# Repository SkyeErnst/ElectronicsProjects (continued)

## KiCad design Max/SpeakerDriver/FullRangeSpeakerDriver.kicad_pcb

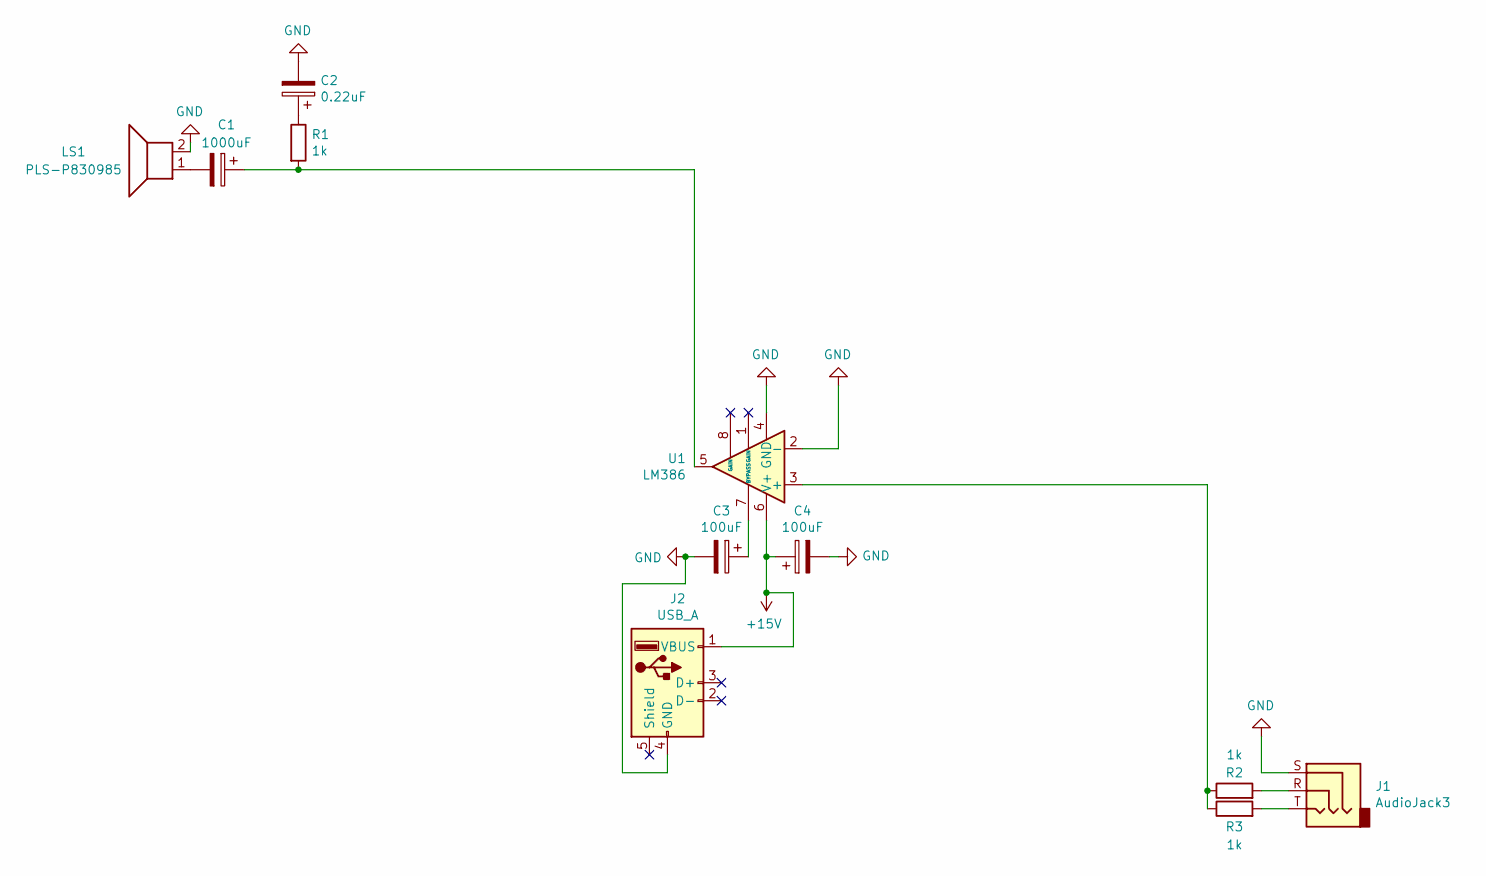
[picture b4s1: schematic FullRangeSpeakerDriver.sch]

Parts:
C1: 1000uF; CP_Radial_D10.0mm_P5.00mm
C2: 0.22uF; CP_Radial_D5.0mm_P2.50mm
C3, C4: 100uF; CP_Radial_D5.0mm_P2.50mm
J1: AudioJack3; PinSocket_1x03_P2.54mm_Vertical
J2: USB_A; USB_A_Stewart_SS-52100-001_Horizontal
LS1: PLS-P830985; PinSocket_1x02_P2.54mm_Vertical
R1, R2, R3: 1k; R_Axial_DIN0207_L6.3mm_D2.5mm_P10.16mm_Horizontal
U1: LM386; DIP-8_W7.62mm

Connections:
+15V: C4.1, J2.1 (VBUS), U1.6 (V+)
GND: C2.2, C3.2, C4.2, J1.S, J2.4 (GND), LS1.2, U1.2 (-), U1.4 (GND)
unnamed: C1.1, R1.2, U1.5
unnamed: C1.2, LS1.1
unnamed: C2.1, R1.1
unnamed: C3.1, U1.7 (BYPASS)
unnamed: J1.R, R2.2
unnamed: J1.T, R3.2
unnamed: R2.1, R3.1, U1.3 (+)

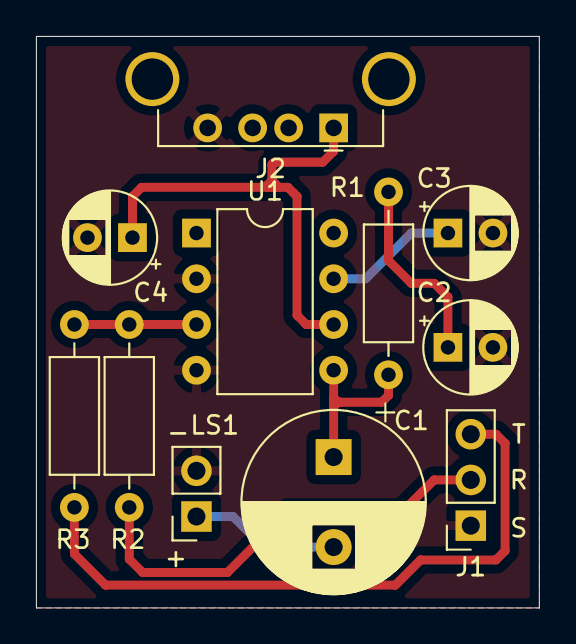
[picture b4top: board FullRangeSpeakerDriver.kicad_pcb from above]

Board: 2 copper layers, 27.9 x 31.7 mm, 11 parts (0 on the bottom side), 9 nets.

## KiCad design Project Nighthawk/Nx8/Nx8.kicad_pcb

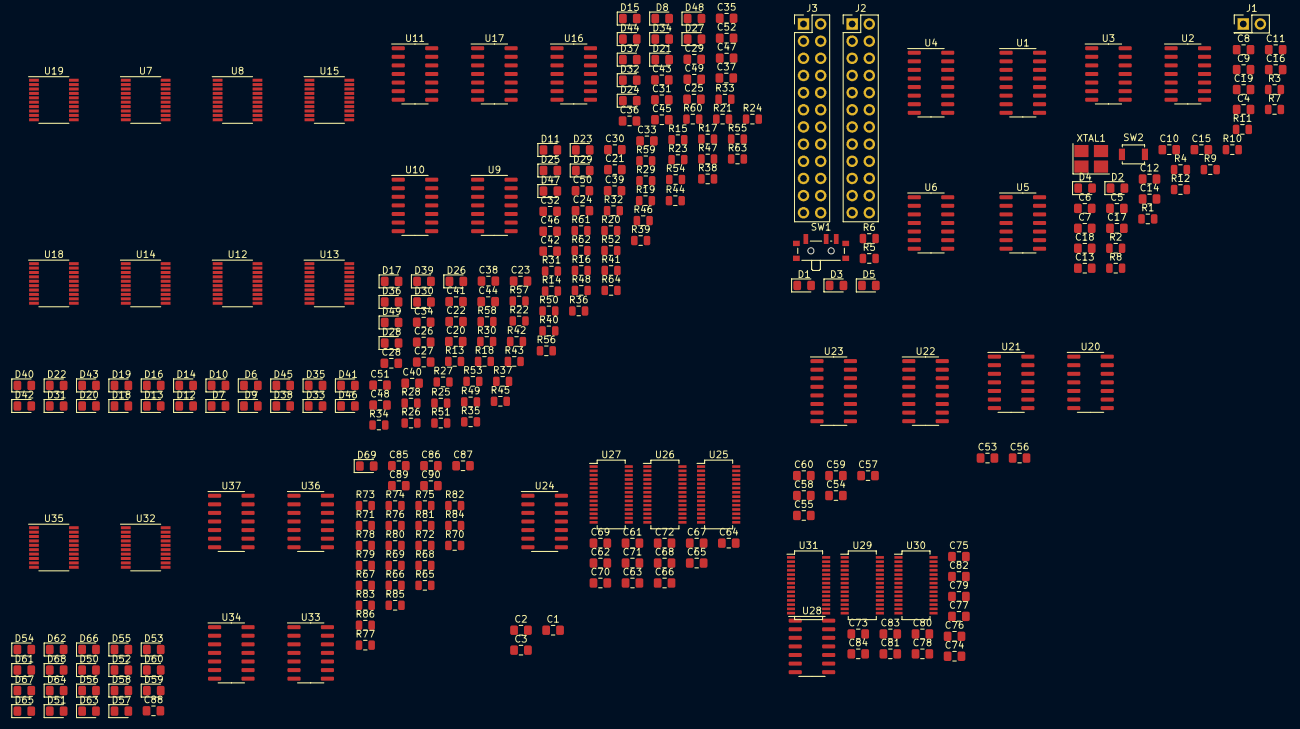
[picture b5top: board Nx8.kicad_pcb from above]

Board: 2 copper layers, 288 parts (0 on the bottom side), 285 nets, no tracks yet.

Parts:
C1, C7, C10, C11, C14, C17, C24, C25, C26, C27, C36, C37, C38, C39, C44, C47, C48, C61, C62, C67, C70, C73, C74, C79, C82, C87, C90: 1nF; C_0805_2012Metric_Pad1.15x1.40mm_HandSolder
C2, C6, C9, C12, C15, C18, C22, C23, C28, C29, C34, C35, C40, C41, C45, C49, C50, C63, C64, C68, C71, C75, C76, C80, C83, C86, C89: 10nF; C_0805_2012Metric_Pad1.15x1.40mm_HandSolder
C3, C5, C8, C13, C16, C19, C20, C21, C30, C31, C32, C33, C42, C43, C46, C51, C52, C65, C66, C69, C72, C77, C78, C81, C84, C85, C88: 100nF; C_0805_2012Metric_Pad1.15x1.40mm_HandSolder
C4, C53, C55, C57, C59: 1uF; C_0805_2012Metric_Pad1.15x1.40mm_HandSolder
C54, C56, C58, C60: 0.1uF; C_0805_2012Metric_Pad1.15x1.40mm_HandSolder
D1: HAULT_RED; LED_0805_2012Metric_Pad1.15x1.40mm_HandSolder
D2: RUN_WHITE; LED_0805_2012Metric_Pad1.15x1.40mm_HandSolder
D3: IDLE_YELLOW; LED_0805_2012Metric_Pad1.15x1.40mm_HandSolder
D4: ~CLK_GREEN; LED_0805_2012Metric_Pad1.15x1.40mm_HandSolder
D5: CLK_GREEN; LED_0805_2012Metric_Pad1.15x1.40mm_HandSolder
D6, D7, D8, D9, D10, D11, D12, D13, D14, D15, D16, D17, D18, D19, D20, D21, D22, D23, D25, D26, D28, D29, D30, D31, D32, D33, D34, D35, D36, D37, D38, D39, D40, D41, D42, D43, D44, D45, D47, D48, D50, D51, D52, D53, D54, D55, D56, D57, D58, D59, D60, D61, D62, D63, D64, D65, D66, D67, D68, D69: GREEN; LED_0805_2012Metric_Pad1.15x1.40mm_HandSolder
D24, D27, D46, D49: RED; LED_0805_2012Metric_Pad1.15x1.40mm_HandSolder
J1: Main_Clock; PinHeader_2x01_P2.54mm_Vertical
J2: Clock Divider Jumper A; PinHeader_2x12_P2.54mm_Vertical
J3: Clock Divider Jumper B; PinHeader_2x12_P2.54mm_Vertical
R1, R2: 10k; R_0805_2012Metric
R3, R5, R6, R7, R15, R16, R17, R18, R19, R20, R21, R22, R23, R24, R25, R26, R27, R28, R29, R30, R33, R34, R36, R37, R41, R42, R43, R44, R45, R46, R47, R48, R49, R50, R51, R52, R53, R54, R55, R56, R59, R60, R62, R63, R66, R67, R68, R69, R70, R71, R72, R73, R74, R75, R77, R78, R79, R80, R81, R82, R83, R84, R85, R86: 220; R_0805_2012Metric
R4, R8, R9, R10, R11, R12, R13, R14, R31, R32, R35, R38, R39, R40, R57, R58, R61, R64, R65, R76: 1k; R_0805_2012Metric
SW1: Clock Start/Stop; SW_SPDT_PCM12
SW2: Clock_Pulse; SW_SPST_B3U-1000P
U1, U4: 74HC4040; SOIC-16_3.9x9.9mm_P1.27mm
U2: 74AHC14; SOIC-14_3.9x8.7mm_P1.27mm
U3: 74AHC00; SOIC-14_3.9x8.7mm_P1.27mm
U5, U6: 74AHC32; SOIC-14_3.9x8.7mm_P1.27mm
U7, U8, U14, U15, U32, U35: 74AHC273; TSSOP-20_4.4x6.5mm_P0.65mm
U9, U10, U16, U33, U36: 74AHC08; SOIC-14_3.9x8.7mm_P1.27mm
U11, U17, U24, U28, U34, U37: 74AHC04; SOIC-14_3.9x8.7mm_P1.27mm
U12, U13, U18, U19: 74AHC245; TSSOP-20_4.4x6.5mm_P0.65mm
U20, U21: 74LS04; SOIC-14_3.9x8.7mm_P1.27mm
U22, U23: 74LS283; SOIC-16_3.9x9.9mm_P1.27mm
U25, U26, U27, U29, U30, U31: IDTQS3390; SSOP-28_3.9x9.9mm_P0.635mm
XTAL1: MXO45-2C-1M000000; Crystal_SMD_TXC_7M-4Pin_3.2x2.5mm_HandSoldering

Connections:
+5V: C4.2, C5.1, C6.1, C7.1, C8.1, C9.1, C10.1, C11.1, C12.1, C13.1, C14.1, C15.1, C16.1, C17.1, C18.1, C19.1, C53.1, C54.1, C55.1, C56.1, C57.1, C58.1, C59.1, C60.1, R13.1, R14.1, R31.1, R32.1, R39.1, R40.1, R57.1, R58.1, R65.1, R76.1, SW1.2, U1.16, U2.14, U3.14, U4.16, U5.14, U12.1, U13.1, U18.1, U19.1, U20.14, U21.14, U22.7, U22.16, U23.16, XTAL1.3
/ALU/ALU Register A Switch Input/ALU_RA_IN_0: U27.25, U32.18
/ALU/ALU Register A Switch Input/ALU_RA_IN_1: U27.22, U32.17
/ALU/ALU Register A Switch Input/ALU_RA_IN_2: U27.19, U32.14
/ALU/ALU Register A Switch Input/ALU_RA_IN_3: U27.16, U32.13
/ALU/ALU Register A Switch Input/ALU_RA_IN_4: U27.12, U32.8
/ALU/ALU Register A Switch Input/ALU_RA_IN_5: U27.9, U32.7
/ALU/ALU Register A Switch Input/ALU_RA_IN_6: U27.6, U32.4
/ALU/ALU Register A Switch Input/ALU_RA_IN_7: U27.3, U32.3
/ALU/ALU Register B Switch Input/ALU_OP_7: U28.1, U28.3, U29.13, U30.13
/ALU/ALU Register B Switch Input/ALU_OP_8: U28.5, U31.13
/ALU/ALU Register B Switch Input/ALU_RB_IN_0: U31.25, U35.18
/ALU/ALU Register B Switch Input/ALU_RB_IN_1: U31.22, U35.17
/ALU/ALU Register B Switch Input/ALU_RB_IN_2: U31.19, U35.14
/ALU/ALU Register B Switch Input/ALU_RB_IN_3: U31.16, U35.13
/ALU/ALU Register B Switch Input/ALU_RB_IN_4: U31.12, U35.8
/ALU/ALU Register B Switch Input/ALU_RB_IN_5: U31.9, U35.7
/ALU/ALU Register B Switch Input/ALU_RB_IN_6: U31.6, U35.4
/ALU/ALU Register B Switch Input/ALU_RB_IN_7: U31.3, U35.3
/ALU/ALU_OP_4: U24.1, U24.3, U25.13, U26.13
/ALU/ALU_OP_5: U24.5, U27.13
/ALU/ALU_REG_BANK/ALU_A_0: R66.1, U32.19
/ALU/ALU_REG_BANK/ALU_A_1: R67.1, U32.16
/ALU/ALU_REG_BANK/ALU_A_2: R68.1, U32.15
/ALU/ALU_REG_BANK/ALU_A_3: R69.1, U32.12
/ALU/ALU_REG_BANK/ALU_A_4: R70.1, U32.9
/ALU/ALU_REG_BANK/ALU_A_5: R71.1, U32.6
/ALU/ALU_REG_BANK/ALU_A_6: R72.1, U32.5
/ALU/ALU_REG_BANK/ALU_A_7: R73.1, U32.2
/ALU/ALU_REG_BANK/ALU_B_0: R77.1, U35.19
/ALU/ALU_REG_BANK/ALU_B_1: R78.1, U35.16
/ALU/ALU_REG_BANK/ALU_B_2: R79.1, U35.15
/ALU/ALU_REG_BANK/ALU_B_3: R80.1, U35.12
/ALU/ALU_REG_BANK/ALU_B_4: R81.1, U35.9
/ALU/ALU_REG_BANK/ALU_B_5: R82.1, U35.6
/ALU/ALU_REG_BANK/ALU_B_6: R83.1, U35.5
/ALU/ALU_REG_BANK/ALU_B_7: R84.1, U35.2
/ALU/ALU_REG_BANK/CLK: U33.1, U36.1
/ALU/ALU_REG_BANK/~RESET: R65.2, R76.2, U32.1, U35.1
/ALU/A_0: R15.1, U7.19, U12.9, U25.27, U29.27
/ALU/A_1: R17.1, U7.16, U12.8, U25.24, U29.24
/ALU/A_2: R19.1, U7.15, U12.7, U25.21, U29.21
/ALU/A_3: R21.1, U7.12, U12.6, U25.18, U29.18
/ALU/A_4: R23.1, U7.9, U12.5, U25.10, U29.10
/ALU/A_5: R25.1, U7.6, U12.4, U25.7, U29.7
/ALU/A_6: R27.1, U7.5, U12.3, U25.4, U29.4
/ALU/A_7: R29.1, U7.2, U12.2, U25.1, U29.1
/ALU/B_0: R41.1, U14.19, U18.9, U25.26, U29.26
/ALU/B_1: R43.1, U14.16, U18.8, U25.23, U29.23
/ALU/B_2: R45.1, U14.15, U18.7, U25.20, U29.20
/ALU/B_3: R47.1, U14.12, U18.6, U25.17, U29.17
/ALU/B_4: R49.1, U14.9, U18.5, U25.11, U29.11
/ALU/B_5: R51.1, U14.6, U18.4, U25.8, U29.8
/ALU/B_6: R53.1, U14.5, U18.3, U25.5, U29.5
/ALU/B_7: R55.1, U14.2, U18.2, U25.2, U29.2
/ALU/C_0: R16.1, U8.19, U13.9, U26.27, U30.27
/ALU/C_1: R18.1, U8.16, U13.8, U26.24, U30.24
/ALU/C_2: R20.1, U8.15, U13.7, U26.21, U30.21
/ALU/C_3: R22.1, U8.12, U13.6, U26.18, U30.18
/ALU/C_4: R24.1, U8.9, U13.5, U26.10, U30.10
/ALU/C_5: R26.1, U8.6, U13.4, U26.7, U30.7
/ALU/C_6: R28.1, U8.5, U13.3, U26.4, U30.4
/ALU/C_7: R30.1, U8.2, U13.2, U26.1, U30.1
/ALU/D_0: R42.1, U15.19, U19.9, U26.26, U30.26
/ALU/D_1: R44.1, U15.16, U19.8, U26.23, U30.23
/ALU/D_2: R46.1, U15.15, U19.7, U26.20, U30.20
/ALU/D_3: R48.1, U15.12, U19.6, U26.17, U30.17
/ALU/D_4: R50.1, U15.9, U19.5, U26.11, U30.11
/ALU/D_5: R52.1, U15.6, U19.4, U26.8, U30.8
/ALU/D_6: R54.1, U15.5, U19.3, U26.5, U30.5
/ALU/D_7: R56.1, U15.2, U19.2, U26.2, U30.2
/ClockCircuit/~HAULT: U2.11, U3.10
/ClockCircuit/~RESET: U1.11, U4.11
/RegisterBank/BUS_0: U7.18, U8.18, U12.11, U13.11, U14.18, U15.18, U18.11, U19.11
/RegisterBank/BUS_1: U7.17, U8.17, U12.12, U13.12, U14.17, U15.17, U18.12, U19.12
/RegisterBank/BUS_2: U7.14, U8.14, U12.13, U13.13, U14.14, U15.14, U18.13, U19.13
/RegisterBank/BUS_3: U7.13, U8.13, U12.14, U13.14, U14.13, U15.13, U18.14, U19.14
/RegisterBank/BUS_4: U7.8, U8.8, U12.15, U13.15, U14.8, U15.8, U18.15, U19.15
/RegisterBank/BUS_5: U7.7, U8.7, U12.16, U13.16, U14.7, U15.7, U18.16, U19.16
/RegisterBank/BUS_6: U7.4, U8.4, U12.17, U13.17, U14.4, U15.4, U18.17, U19.17
/RegisterBank/BUS_7: U7.3, U8.3, U12.18, U13.18, U14.3, U15.3, U18.18, U19.18
/RegisterBank/CLK: U9.1, U9.4, U10.1, U16.1
/RegisterBank/~OE_A: R31.2, U11.3, U12.19
/RegisterBank/~OE_B: R57.2, U11.9, U18.19
/RegisterBank/~OE_C: R32.2, U11.13, U13.19
/RegisterBank/~OE_D: R58.2, U17.3, U19.19
/RegisterBank/~RESET: R13.2, R14.2, R39.2, R40.2, U7.1, U8.1, U14.1, U15.1
GND: C1.2, C2.2, C3.2, C4.1, C5.2, C6.2, C7.2, C8.2, C9.2, C10.2, C11.2, C12.2, C13.2, C14.2, C15.2, C16.2, C17.2, C18.2, C19.2, C20.2, C21.2, C22.2, C23.2, C24.2, C25.2, C26.2, C27.2, C28.2, C29.2, C30.2, C31.2, C32.2, C33.2, C34.2, C35.2, C36.2, C37.2, C38.2, C39.2, C40.2, C41.2, C42.2, C43.2, C44.2, C45.2, C46.2, C47.2, C48.2, C49.2, C50.2, C51.2, C52.2, C53.2, C54.2, C55.2, C56.2, C57.2, C58.2, C59.2, C60.2, C61.2, C62.2, C63.2, C64.2, C65.2, C66.2, C67.2, C68.2, C69.2, C70.2, C71.2, C72.2, C73.2, C74.2, C75.2, C76.2, C77.2, C78.2, C79.2, C80.2, C81.2, C82.2, C83.2, C84.2, C85.2, C86.2, C87.2, C88.2, C89.2, C90.2, D6.1, D7.1, D8.1, D9.1, D10.1, D11.1, D12.1, D13.1, D14.1, D15.1, D16.1, D17.1, D18.1, D19.1, D20.1, D21.1, D22.1, D23.1, D24.1, D25.1, D26.1, D27.1, D28.1, D29.1, D30.1, D31.1, D32.1, D33.1, D34.1, D35.1, D36.1, D37.1, D38.1, D39.1, D40.1, D41.1, D42.1, D43.1, D44.1, D45.1, D46.1, D47.1, D48.1, D49.1, D50.1, D51.1, D52.1, D53.1, D54.1, D55.1, D56.1, D57.1, D58.1, D59.1, D60.1, D61.1, D62.1, D63.1, D64.1, D65.1, D66.1, D67.1, D68.1, D69.1, R1.1, R2.1, R3.1, R5.1, R6.1, R7.1, R11.1, R12.1, U1.8, U2.7, U2.13, U3.7, U4.8, U5.4, U5.5, U5.7, U5.9, U5.10, U5.12, U5.13, U6.9, U6.10, U7.10, U8.10, U9.7, U11.7, U12.10, U13.10, U14.10, U15.10, U17.5, U17.7, U17.9, U17.11, U17.13, U18.10, U19.10, U20.7, U21.7, U22.2, U22.6, U22.8, U22.11, U22.15, U23.2, U23.6, U23.8, U23.11, U23.15, U24.7, U24.9, U24.11, U24.13, U25.14, U26.14, U27.14, U28.7, U28.9, U28.11, U28.13, U29.14, U30.14, U31.14, U32.10, U35.10, XTAL1.2
unnamed: C1.1, C2.1, C3.1
unnamed: C20.1, C22.1, C24.1, U7.20
unnamed: C21.1, C23.1, C25.1, U8.20
unnamed: C26.1, C28.1, C30.1, U12.20
unnamed: C27.1, C29.1, C31.1, U13.20
unnamed: C32.1, C34.1, C36.1, U14.20
unnamed: C33.1, C35.1, C37.1, U15.20
unnamed: C38.1, C40.1, C42.1, U18.20
unnamed: C39.1, C41.1, C43.1, U19.20
unnamed: C44.1, C45.1, C46.1, U9.14
unnamed: C47.1, C49.1, C51.1, U11.14
unnamed: C48.1, C50.1, C52.1, U17.14
unnamed: C61.1, C63.1, C65.1, U25.28
unnamed: C62.1, C64.1, C66.1, U26.28
unnamed: C67.1, C68.1, C69.1, U27.28
unnamed: C70.1, C71.1, C72.1, U24.14
unnamed: C73.1, C75.1, C77.1, U29.28
unnamed: C74.1, C76.1, C78.1, U30.28
unnamed: C79.1, C80.1, C81.1, U31.28
unnamed: C82.1, C83.1, C84.1, U28.14
unnamed: C85.1, C86.1, C87.1, U32.20
unnamed: C88.1, C89.1, C90.1, U35.20
unnamed: D1.1, R3.2
unnamed: D1.2, U2.10
unnamed: D2.1, R4.2
unnamed: D2.2, U2.4, U3.2
unnamed: D3.1, R5.2
unnamed: D3.2, U2.6, U2.9
unnamed: D4.1, R6.2
unnamed: D4.2, U3.8, U3.12, U3.13
unnamed: D5.1, R7.2
unnamed: D5.2, U3.11
unnamed: D6.2, R15.2
unnamed: D7.2, R16.2
unnamed: D8.2, R17.2
unnamed: D9.2, R18.2
unnamed: D10.2, R19.2
unnamed: D11.2, R20.2
unnamed: D12.2, R21.2
unnamed: D13.2, R22.2
unnamed: D14.2, R23.2
unnamed: D15.2, R24.2
unnamed: D16.2, R25.2
unnamed: D17.2, R26.2
unnamed: D18.2, R27.2
unnamed: D19.2, R28.2
unnamed: D20.2, R29.2
unnamed: D21.2, R30.2
unnamed: D22.2, R33.1
unnamed: D23.2, R34.1
unnamed: D24.2, R35.1
unnamed: D25.2, R36.1
unnamed: D26.2, R37.1
unnamed: D27.2, R38.1
unnamed: D28.2, R41.2
unnamed: D29.2, R42.2
unnamed: D30.2, R43.2
unnamed: D31.2, R44.2
unnamed: D32.2, R45.2
unnamed: D33.2, R46.2
unnamed: D34.2, R47.2
unnamed: D35.2, R48.2
unnamed: D36.2, R49.2
unnamed: D37.2, R50.2
unnamed: D38.2, R51.2
unnamed: D39.2, R52.2
unnamed: D40.2, R53.2
unnamed: D41.2, R54.2
unnamed: D42.2, R55.2
unnamed: D43.2, R56.2
unnamed: D44.2, R59.1
unnamed: D45.2, R60.1
unnamed: D46.2, R61.1
unnamed: D47.2, R62.1
unnamed: D48.2, R63.1
unnamed: D49.2, R64.1
unnamed: D50.2, R66.2
unnamed: D51.2, R67.2
unnamed: D52.2, R68.2
unnamed: D53.2, R69.2
unnamed: D54.2, R70.2
unnamed: D55.2, R71.2
unnamed: D56.2, R72.2
unnamed: D57.2, R73.2
unnamed: D58.2, R74.1
unnamed: D59.2, R75.1
unnamed: D60.2, R77.2
unnamed: D61.2, R78.2
unnamed: D62.2, R79.2
unnamed: D63.2, R80.2
unnamed: D64.2, R81.2
unnamed: D65.2, R82.2
unnamed: D66.2, R83.2
unnamed: D67.2, R84.2
unnamed: D68.2, R85.1
unnamed: D69.2, R86.1
unnamed: J1.1, U1.10, XTAL1.4
unnamed: J1.2, J2.13, J2.14, J2.15, J2.16, J2.17, J2.18, J2.19, J2.20, J2.21, J2.22, J2.23, J2.24, J3.13, J3.14, J3.15, J3.16, J3.17, J3.18, J3.19, J3.20, J3.21, J3.22, J3.23, J3.24, U3.1
unnamed: J2.1, U1.9
unnamed: J2.2, U1.7
unnamed: J2.3, U1.6
unnamed: J2.4, U1.5
unnamed: J2.5, U1.3
unnamed: J2.6, U1.2
unnamed: J2.7, U1.4
unnamed: J2.8, U1.13
unnamed: J2.9, U1.12
unnamed: J2.10, U1.14
unnamed: J2.11, U1.15
unnamed: J2.12, U1.1, U4.10
unnamed: J3.1, U4.9
unnamed: J3.2, U4.7
unnamed: J3.3, U4.6
unnamed: J3.4, U4.5
unnamed: J3.5, U4.3
unnamed: J3.6, U4.2
unnamed: J3.7, U4.4
unnamed: J3.8, U4.13
unnamed: J3.9, U4.12
unnamed: J3.10, U4.14
unnamed: J3.11, U4.15
unnamed: J3.12, U4.1
unnamed: R1.2, SW1.1, U2.1
unnamed: R2.2, SW2.2, U2.5
unnamed: R4.1, R8.2
unnamed: R8.1, R9.2
unnamed: R10.1, R11.2, R12.2
unnamed: R9.1, R10.2
unnamed: R33.2, U9.2, U11.2
unnamed: R34.2, U7.11, U9.3
unnamed: R35.2, U11.4
unnamed: R36.2, U10.2, U11.10
unnamed: R37.2, U8.11, U10.3
unnamed: R38.2, U11.12
unnamed: R59.2, U9.5, U11.6
unnamed: R60.2, U9.6, U14.11
unnamed: R61.2, U11.8
unnamed: R62.2, U16.2, U17.2
unnamed: R63.2, U15.11, U16.3
unnamed: R64.2, U17.4
unnamed: R74.2, U33.2, U34.2
unnamed: R75.2, U32.11, U33.3
unnamed: R85.2, U36.2, U37.2
unnamed: R86.2, U35.11, U36.3
unnamed: SW1.3, SW2.1
unnamed: U2.2, U2.3
unnamed: U2.8, U5.2
unnamed: U3.3, U3.4, U3.5
unnamed: U3.6, U5.1
unnamed: U3.9, U5.3
unnamed: U20.2, U22.5
unnamed: U20.4, U22.3
unnamed: U20.6, U22.14
unnamed: U20.8, U22.12
unnamed: U20.10, U23.5
unnamed: U20.12, U23.3
unnamed: U21.2, U23.14
unnamed: U21.4, U23.12
unnamed: U22.9, U23.7
unnamed: U24.2, U25.15
unnamed: U24.4, U26.15
unnamed: U24.6, U27.15
unnamed: U25.3, U27.1
unnamed: U25.6, U27.4
unnamed: U25.9, U27.7
unnamed: U25.12, U27.10
unnamed: U25.16, U27.18
unnamed: U25.19, U27.21
unnamed: U25.22, U27.24
unnamed: U25.25, U27.27
unnamed: U26.3, U27.2
unnamed: U26.6, U27.5
unnamed: U26.9, U27.8
unnamed: U26.12, U27.11
unnamed: U26.16, U27.17
unnamed: U26.19, U27.20
unnamed: U26.22, U27.23
unnamed: U26.25, U27.26
unnamed: U28.2, U29.15
unnamed: U28.4, U30.15
unnamed: U28.6, U31.15
unnamed: U29.3, U31.1
unnamed: U29.6, U31.4
unnamed: U29.9, U31.7
unnamed: U29.12, U31.10
unnamed: U29.16, U31.18
unnamed: U29.19, U31.21
unnamed: U29.22, U31.24
unnamed: U29.25, U31.27
unnamed: U30.3, U31.2
unnamed: U30.6, U31.5
unnamed: U30.9, U31.8
unnamed: U30.12, U31.11
unnamed: U30.16, U31.17
unnamed: U30.19, U31.20
unnamed: U30.22, U31.23
unnamed: U30.25, U31.26

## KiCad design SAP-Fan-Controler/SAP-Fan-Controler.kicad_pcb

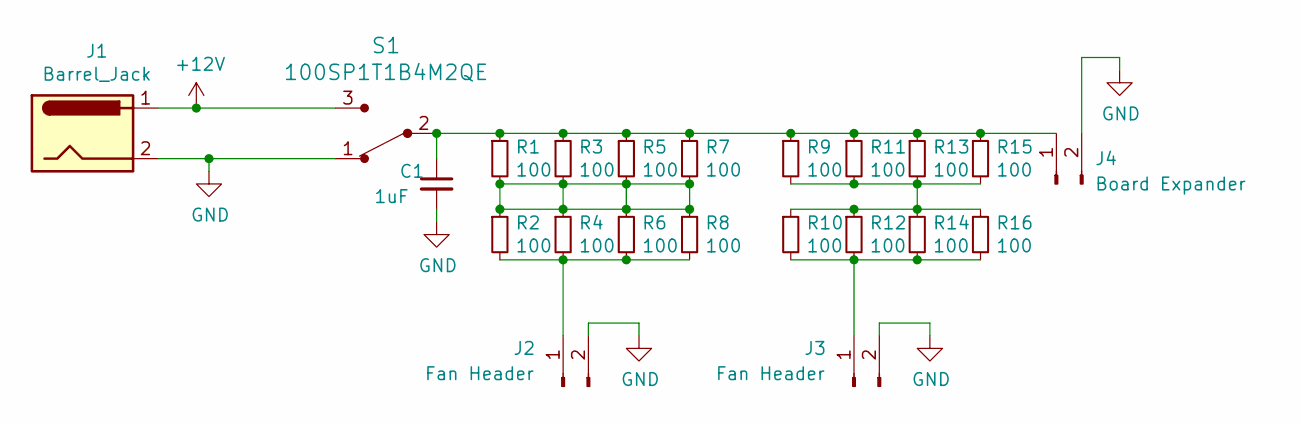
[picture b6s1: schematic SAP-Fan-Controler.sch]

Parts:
C1: 1uF; C_0805_2012Metric_Pad1.15x1.40mm_HandSolder
J1: Barrel_Jack; BarrelJack_CUI_PJ-063AH_Horizontal
J2, J3: Fan Header; PinHeader_1x02_P2.54mm_Vertical
J4: Board Expander; PinHeader_1x02_P2.54mm_Vertical
R1, R2, R3, R4, R5, R6, R7, R8, R9, R10, R11, R12, R13, R14, R15, R16: 100; R_Axial_DIN0309_L9.0mm_D3.2mm_P15.24mm_Horizontal
S1: 100SP1T1B4M2QE; Toggle_Switch_100SP1T1B4M2QE; MPN 100SP1T1B4M2QE; Digi-Key_PN EG2355-ND

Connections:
+12V: J1.1, S1.3
GND: C1.2, J1.2, J2.2, J3.2, J4.2, S1.1
unnamed: C1.1, J4.1, R1.1, R3.1, R5.1, R7.1, R9.1, R11.1, R13.1, R15.1, S1.2 (Com)
unnamed: J2.1, R2.2, R4.2, R6.2, R8.2
unnamed: J3.1, R10.2, R12.2, R14.2, R16.2
unnamed: R1.2, R2.1, R3.2, R4.1, R5.2, R6.1, R7.2, R8.1
unnamed: R9.2, R10.1, R11.2, R12.1, R13.2, R14.1, R15.2, R16.1

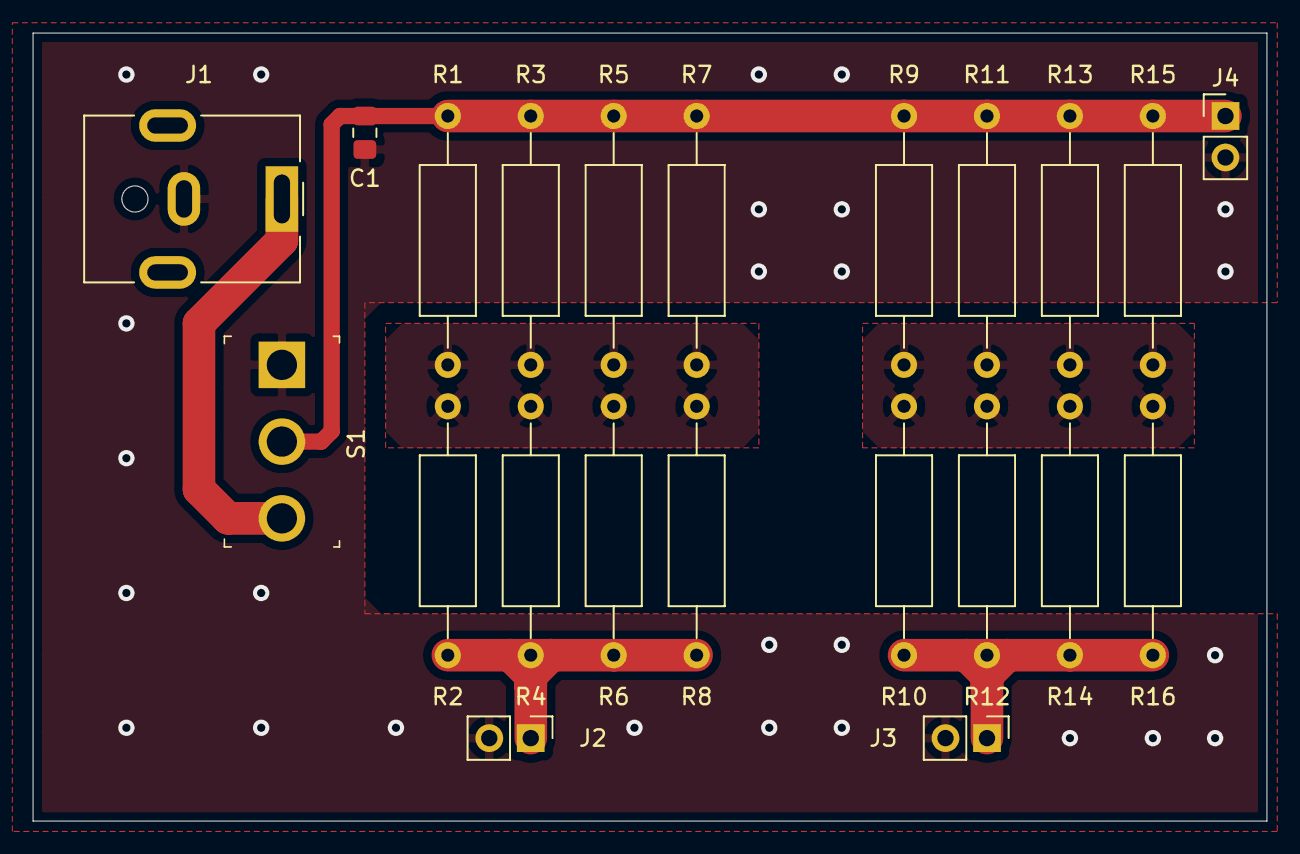
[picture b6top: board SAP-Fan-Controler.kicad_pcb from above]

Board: 2 copper layers, 75.6 x 48.3 mm, 22 parts (0 on the bottom side), 7 nets.
